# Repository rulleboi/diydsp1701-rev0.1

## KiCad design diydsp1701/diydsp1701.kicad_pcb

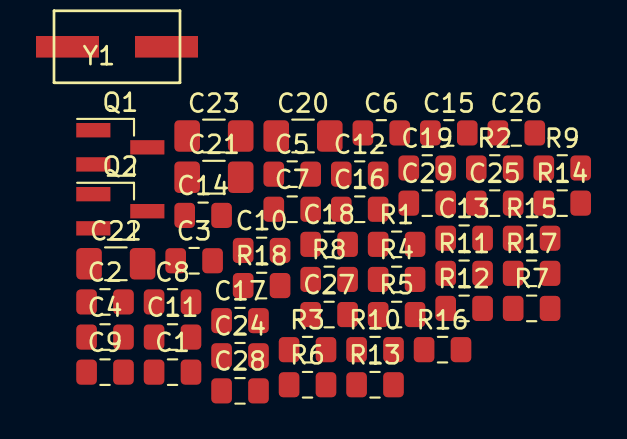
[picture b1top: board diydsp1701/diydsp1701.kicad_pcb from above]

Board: 2 copper layers, 50 parts (0 on the bottom side), 27 nets, no tracks yet.

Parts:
C1, C2: 100p; C_0805_2012Metric_Pad1.15x1.40mm_HandSolder
C3, C4, C7, C8, C12, C13: 10u; C_0805_2012Metric_Pad1.15x1.40mm_HandSolder
C5, C6, C9, C10, C11, C18, C19, C29: 100n; C_0805_2012Metric_Pad1.15x1.40mm_HandSolder
C14: 3n3; C_0805_2012Metric_Pad1.15x1.40mm_HandSolder
C15: 56n; C_0805_2012Metric_Pad1.15x1.40mm_HandSolder
C16, C17: 22p; C_0805_2012Metric_Pad1.15x1.40mm_HandSolder
C20, C21, C22, C23: 47u 4V; C_1206_3216Metric_Pad1.42x1.75mm_HandSolder
C24, C25, C26, C27: 5n6; C_0805_2012Metric_Pad1.15x1.40mm_HandSolder
C28: 330n; C_0805_2012Metric_Pad1.15x1.40mm_HandSolder
Q1: ZXTP25040DFH; SOT-23_Handsoldering
Q2: MMBT2222A-TP; SOT-23_Handsoldering
R1, R2: 47k; C_0805_2012Metric_Pad1.15x1.40mm_HandSolder
R3, R4, R5, R6: 18k0; C_0805_2012Metric_Pad1.15x1.40mm_HandSolder
R7: 1k; C_0805_2012Metric_Pad1.15x1.40mm_HandSolder
R8, R11, R12, R13, R14: 10k; C_0805_2012Metric_Pad1.15x1.40mm_HandSolder
R9: 100R; C_0805_2012Metric_Pad1.15x1.40mm_HandSolder
R10: 470R; C_0805_2012Metric_Pad1.15x1.40mm_HandSolder
R15, R16, R17, R18: 560R; C_0805_2012Metric_Pad1.15x1.40mm_HandSolder
Y1: 12.288MHz; ABLS7M2

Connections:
+1V8: C8.1, C9.1, C19.1, Q1.3, R14.2
+3V3: C14.1, C15.1, C18.1, C29.1, R3.2, R8.2, R11.2, R12.2, R13.2
/CM: C11.2, C13.2
/FILTA: C6.1, C7.1
/FILTD: C10.1, C12.1
/IN0: C1.1, C3.1, R1.2
/IN1: C2.1, C4.1, R2.2
/MCLKI: C16.1, Y1.2
/OUT0: C24.1, R15.1
/OUT1: C25.1, R16.1
/OUT2: C26.1, R17.1
/OUT3: C27.1, R18.1
/VDRIVE: Q1.1, R7.2
/_RESET: C5.1, R3.1
GND: C1.2, C2.2, C5.2, C6.2, C7.2, C8.2, C9.2, C10.2, C11.1, C12.2, C13.1, C16.2, C17.2, C18.2, C19.2, C24.2, C25.2, C26.2, C27.2, C28.2, C29.2, Q2.2, R1.1, R2.1, R5.2
unnamed: C3.2, R4.2
unnamed: C4.2, R6.2
unnamed: C14.2, R10.2
unnamed: C15.2, R10.1
unnamed: C17.1, R9.1, Y1.1
unnamed: C20.2, R15.2
unnamed: C21.2, R16.2
unnamed: C22.2, R17.2
unnamed: C23.2, R18.2
unnamed: Q1.2, R7.1
unnamed: Q2.1, R14.1
WB: Q2.3, R13.1

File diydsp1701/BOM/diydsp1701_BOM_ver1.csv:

Id;Designator;Package;Quantity;Designation;Supplier and ref;Price/per;Max total price DKK;Comment
1;U1;LQFP-48_7x7mm_Pitch0.5mm;1;ADAU1701JSTZ;http://www.digikey.dk/product-detail/en/analog-devices-inc/A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;72,9;72,9;locked
2;C1,C2;C_0805_HandSoldering;2;100p;http://www.digikey.dk/product-detail/en/kemet/C0805C101J5GAC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;0,68;1,36;
3;C3,C4,C7,C8,C12,C13;C_0805_HandSoldering;6;10u;http://www.digikey.dk/product-detail/en/murata-electronics-n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;0,95;5,7;
4;C5;C_0805_HandSoldering;1;10n;http://www.digikey.dk/product-detail/en/yageo/CC0805KRX7R9BB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;0,68;0,68;
5;C6,C9,C10,C11,C18,C19,C29;C_0805_HandSoldering;7;100n;http://www.digikey.dk/product-detail/en/avx-corporation/0805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;0,68;4,76;
6;C14;C_0805_HandSoldering;1;3n3;http://www.digikey.dk/product-detail/en/kemet/C0805C332K5RAC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;0,68;0,68;
7;C15;C_0805_HandSoldering;1;56n;http://www.digikey.dk/product-detail/en/samsung-electro-mech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;0,88;0,88;
8;C16,C17;C_0805_HandSoldering;2;22p;http://www.digikey.dk/product-detail/en/kemet/C0805C220J5GAC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;0,68;1,36;
9;C20,C21,C22,C23;C_0805_HandSoldering;4;47u 4V;http://www.digikey.dk/product-detail/en/kemet/T520A476M004AT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;6,95;27,8;1206
10;C24,C25,C26,C27;C_0805_HandSoldering;4;5n6;http://www.digikey.dk/product-detail/en/yageo/CC0805KRX7R9BB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;0,68;2,72;
11;P1,P5,P6;JST_PH_B3B-PH-K_03x2.00mm_Straight;3;CONN_01X03;http://www.digikey.dk/product-detail/en/jst-sales-america-in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;1,28;3,84;
12;R1,R2;R_0805_HandSoldering;2;47k;http://www.digikey.dk/product-detail/en/yageo/RC0805JR-0747K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;0,68;1,36;
13;R3,R4,R5,R6;R_0805_HandSoldering;4;18k0;http://www.digikey.dk/product-detail/en/yageo/RC0805FR-0718K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;0,68;2,72;1%
14;R7;R_0805_HandSoldering;1;1k;http://www.digikey.dk/product-detail/en/yageo/RC0805FR-071KL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;0,68;0,68;
15;R8,R11,R12,R13,R14;R_0805_HandSoldering;5;10k;http://www.digikey.dk/product-detail/en/yageo/RC0805JR-0710K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;0,68;3,4;
16;R9;R_0805_HandSoldering;1;100R;http://www.digikey.dk/product-detail/en/yageo/RC0805FR-07100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;0,68;0,68;
17;R10;R_0805_HandSoldering;1;470R;http://www.digikey.dk/product-detail/en/yageo/RC0805FR-07470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;0,68;0,68;
18;U2;SOIC-8_3.9x4.9mm_Pitch1.27mm;1;24AA256;http://www.digikey.dk/product-detail/en/microchip-technology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;5,13;5,13;locked
19;R15,R16,R17,R18;R_0805_HandSoldering;4;560R;http://www.digikey.dk/product-detail/en/yageo/RC0805FR-07560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;0,68;2,72;
20;Q2;SOT-23_Handsoldering;1;MMBT2222A-TP;http://www.digikey.dk/product-detail/en/micro-commercial-co/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;0,95;0,95;locked
21;Q1;SOT-23_Handsoldering;1;ZXTP25040DFH;http://www.digikey.dk/product-search/en?keywords=ZXTP25040DFH;3,92;3,92;locked
22;P2;Pin_Header_Straight_1x03;1;CONN_01X03;http://www.digikey.dk/product-detail/en/harwin-inc/M20-99903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;0,68;0,68;
23;P3;Pin_Header_Straight_1x02;1;CONN_01X02;http://www.digikey.dk/product-detail/en/harwin-inc/M20-99902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;0,68;0,68;
24;Y1;ABLS7M2;1;12.288MHz;http://www.digikey.dk/product-detail/en/abracon-llc/ABLS7M2-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;2,57;2,57;locked
25;C28;C_0805_HandSoldering;1;330n 25V;http://www.digikey.dk/product-detail/en/avx-corporation/0805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;0,68;0,68;
26;U3;SOT-223;1;UA78M33CDCYR;http://www.digikey.dk/product-detail/en/texas-instruments/UA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;3,92;3,92;locked
27;P7;JST_PH_B2B-PH-K_02x2.00mm_Straight;1;CONN_01X02;http://www.digikey.dk/product-detail/en/jst-sales-america-in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;1,15;1,15;
28;REF**,REF**,REF**,REF**;MountingHole_3.2mm_M3_Pad_Via;4;MountingHole_3.2mm_M3_Pad_Via;-;0;0;
29;P4;Pin_Header_Straight_1x12;1;CONN_01X12;http://www.digikey.dk/product-detail/en/sullins-connector-so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;2,23;2,23;
;;;;;;;156,83;

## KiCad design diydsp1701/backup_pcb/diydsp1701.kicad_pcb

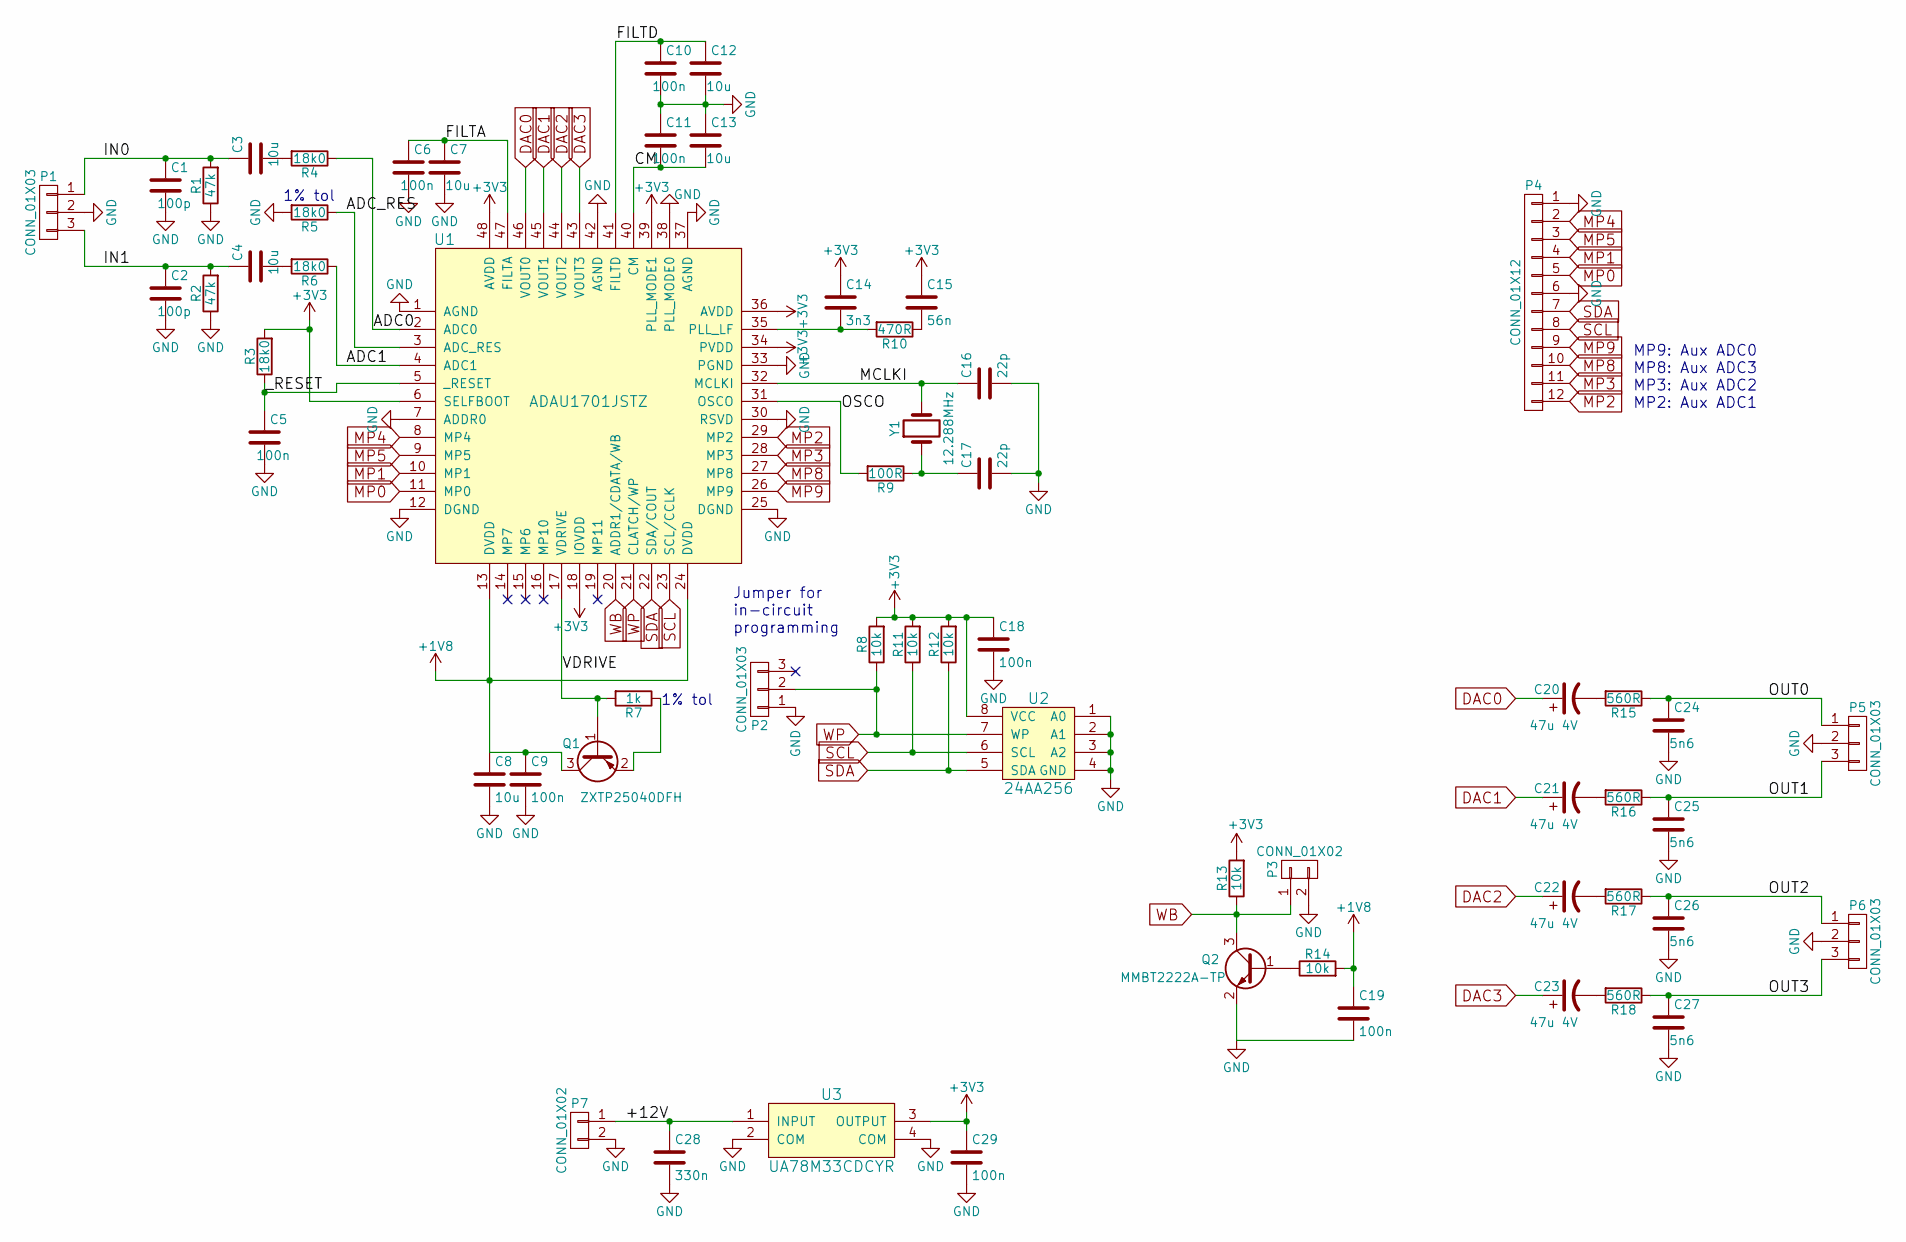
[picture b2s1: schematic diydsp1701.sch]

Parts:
C1, C2: 100p; C_0805_2012Metric_Pad1.15x1.40mm_HandSolder
C3, C4, C7, C8, C12, C13: 10u; C_0805_2012Metric_Pad1.15x1.40mm_HandSolder
C5, C6, C9, C10, C11, C18, C19, C29: 100n; C_0805_2012Metric_Pad1.15x1.40mm_HandSolder
C14: 3n3; C_0805_2012Metric_Pad1.15x1.40mm_HandSolder
C15: 56n; C_0805_2012Metric_Pad1.15x1.40mm_HandSolder
C16, C17: 22p; C_0805_2012Metric_Pad1.15x1.40mm_HandSolder
C20, C21, C22, C23: 47u 4V; C_1206_3216Metric_Pad1.42x1.75mm_HandSolder
C24, C25, C26, C27: 5n6; C_0805_2012Metric_Pad1.15x1.40mm_HandSolder
C28: 330n; C_0805_2012Metric_Pad1.15x1.40mm_HandSolder
P1, P5, P6: CONN_01X03; JST_PH_B3B-PH-K_03x2.00mm_Straight
P2: CONN_01X03; Pin_Header_Straight_1x03
P3: CONN_01X02; Pin_Header_Straight_1x02
P4: CONN_01X12; Pin_Header_Straight_1x12
P7: CONN_01X02; JST_PH_B2B-PH-K_02x2.00mm_Straight
Q1: ZXTP25040DFH; SOT-23_Handsoldering
Q2: MMBT2222A-TP; SOT-23_Handsoldering
R1, R2: 47k; C_0805_2012Metric_Pad1.15x1.40mm_HandSolder
R3, R4, R5, R6: 18k0; C_0805_2012Metric_Pad1.15x1.40mm_HandSolder
R7: 1k; C_0805_2012Metric_Pad1.15x1.40mm_HandSolder
R8, R11, R12, R13, R14: 10k; C_0805_2012Metric_Pad1.15x1.40mm_HandSolder
R9: 100R; C_0805_2012Metric_Pad1.15x1.40mm_HandSolder
R10: 470R; C_0805_2012Metric_Pad1.15x1.40mm_HandSolder
R15, R16, R17, R18: 560R; C_0805_2012Metric_Pad1.15x1.40mm_HandSolder
U1: ADAU1701JSTZ; LQFP-48_7x7mm_Pitch0.5mm
U2: 24AA256; SOIC-8_3.9x4.9mm_Pitch1.27mm
U3: UA78M33CDCYR; SOT-223
Y1: 12.288MHz; ABLS7M2

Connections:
+1V8: C8.1, C9.1, C19.1, Q1.3 (C), R14.2, U1.13 (DVDD), U1.24 (DVDD)
+3V3: C14.1, C15.1, C18.1, C29.1, R3.2, R8.2, R11.2, R12.2, R13.2, U1.6 (SELFBOOT), U1.18 (IOVDD), U1.34 (PVDD), U1.36 (AVDD), U1.39 (PLL_MODE1), U1.48 (AVDD), U2.8 (VCC), U3.3 (OUTPUT)
/+12V: C28.1, P7.1, U3.1 (INPUT)
/ADC0: R4.1, U1.2 (ADC0)
/ADC1: R6.1, U1.4 (ADC1)
/ADC_RES: R5.1, U1.3 (ADC_RES)
/CM: C11.2, C13.2, U1.40 (CM)
/FILTA: C6.1, C7.1, U1.47 (FILTA)
/FILTD: C10.1, C12.1, U1.41 (FILTD)
/IN0: C1.1, C3.1, P1.1, R1.2
/IN1: C2.1, C4.1, P1.3, R2.2
/MCLKI: C16.1, U1.32 (MCLKI), Y1.2
/OSCO: R9.2, U1.31 (OSCO)
/OUT0: C24.1, P5.1, R15.1
/OUT1: C25.1, P5.3, R16.1
/OUT2: C26.1, P6.1, R17.1
/OUT3: C27.1, P6.3, R18.1
/VDRIVE: Q1.1 (B), R7.2, U1.17 (VDRIVE)
/_RESET: C5.1, R3.1, U1.5 (_RESET)
DAC0: C20.1, U1.46 (VOUT0)
DAC1: C21.1, U1.45 (VOUT1)
DAC2: C22.1, U1.44 (VOUT2)
DAC3: C23.1, U1.43 (VOUT3)
GND: C1.2, C2.2, C5.2, C6.2, C7.2, C8.2, C9.2, C10.2, C11.1, C12.2, C13.1, C16.2, C17.2, C18.2, C19.2, C24.2, C25.2, C26.2, C27.2, C28.2, C29.2, P1.2, P2.1, P3.2, P4.1, P4.6, P5.2, P6.2, P7.2, Q2.2 (E), R1.1, R2.1, R5.2, U1.1 (AGND), U1.7 (ADDR0), U1.12 (DGND), U1.25 (DGND), U1.30 (RSVD), U1.33 (PGND), U1.37 (AGND), U1.38 (PLL_MODE0), U1.42 (AGND), U2.1 (A0), U2.2 (A1), U2.3 (A2), U2.4 (GND), U3.2 (COM), U3.4 (COM)
MP0: P4.5, U1.11 (MP0)
MP1: P4.4, U1.10 (MP1)
MP2: P4.12, U1.29 (MP2)
MP3: P4.11, U1.28 (MP3)
MP4: P4.2, U1.8 (MP4)
MP5: P4.3, U1.9 (MP5)
MP8: P4.10, U1.27 (MP8)
MP9: P4.9, U1.26 (MP9)
unnamed: C3.2, R4.2
unnamed: C4.2, R6.2
unnamed: C14.2, R10.2, U1.35 (PLL_LF)
unnamed: C15.2, R10.1
unnamed: C17.1, R9.1, Y1.1
unnamed: C20.2, R15.2
unnamed: C21.2, R16.2
unnamed: C22.2, R17.2
unnamed: C23.2, R18.2
unnamed: Q1.2 (E), R7.1
unnamed: Q2.1 (B), R14.1
SCL: P4.8, R11.1, U1.23 (SCL/CCLK), U2.6 (SCL)
SDA: P4.7, R12.1, U1.22 (SDA/COUT), U2.5 (SDA)
WB: P3.1, Q2.3 (C), R13.1, U1.20 (ADDR1/CDATA/WB)
WP: P2.2, R8.1, U1.21 (CLATCH/WP), U2.7 (WP)

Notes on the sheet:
1% tol
Jumper for in-circuit programming
MP9: Aux ADC0 MP8: Aux ADC3 MP3: Aux ADC2 MP2: Aux ADC1

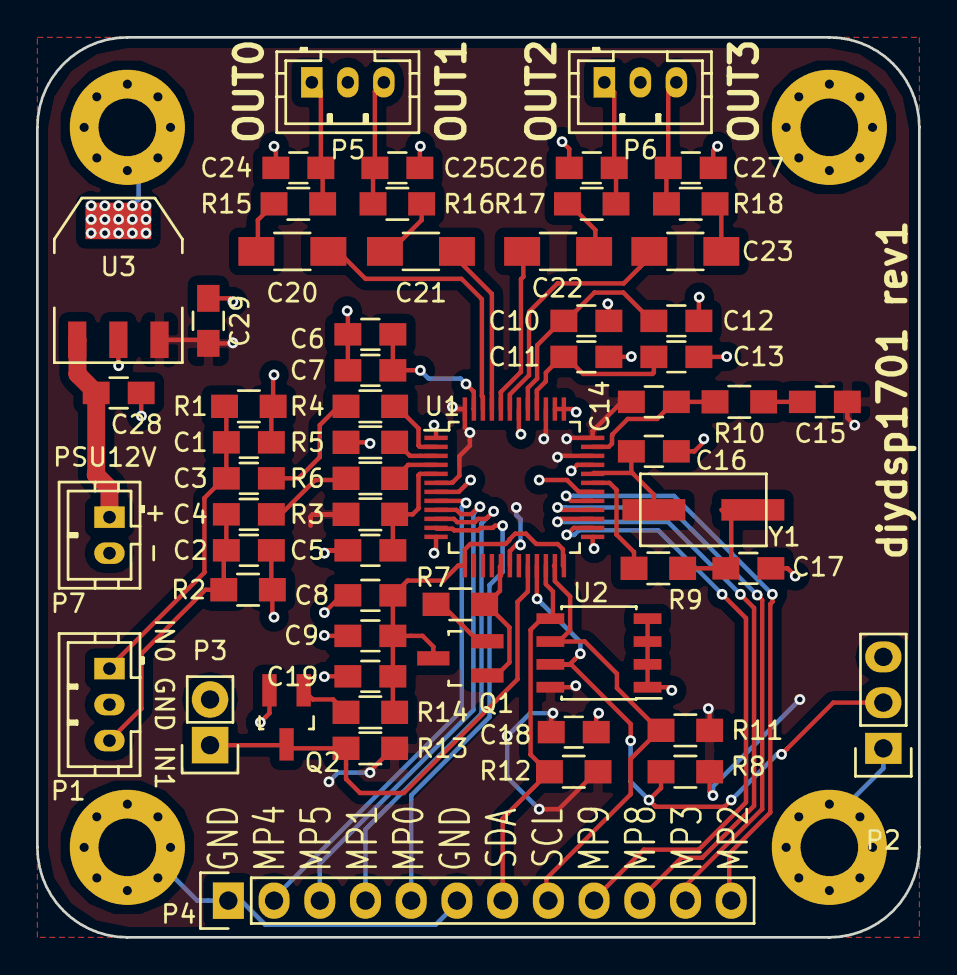
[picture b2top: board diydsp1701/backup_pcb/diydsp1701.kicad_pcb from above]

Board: 2 copper layers, 49.0 x 50.0 mm, 60 parts (0 on the bottom side), 47 nets.

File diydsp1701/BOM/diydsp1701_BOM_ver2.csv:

Id;Designator;Package;Quantity;Designation;Supplier and ref;Price/per;Max total price DKK;Comment;Amount to buy 14 Nov 2016
1;U1;LQFP-48_7x7mm_Pitch0.5mm;1;ADAU1701JSTZ;http://www.digikey.dk/product-detail/en/analog-devices-inc/A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;72,9;72,9;locked;2
2;C1,C2;C_0805_HandSoldering;2;100p;http://www.digikey.dk/product-detail/en/kemet/C0805C101J5GAC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;0,68;1,36;;
3;C3,C4,C7,C8,C12,C13;C_0805_HandSoldering;6;10u;http://www.digikey.dk/product-detail/en/murata-electronics-n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;0,95;5,7;;
4;C5;C_0805_HandSoldering;1;10n;http://www.digikey.dk/product-detail/en/yageo/CC0805KRX7R9BB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;0,68;0,68;;
5;C6,C9,C10,C11,C18,C19,C29;C_0805_HandSoldering;7;100n;http://www.digikey.dk/product-detail/en/avx-corporation/0805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;0,68;4,76;;
6;C14;C_0805_HandSoldering;1;3n3;http://www.digikey.dk/product-detail/en/kemet/C0805C332K5RAC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;0,68;0,68;;
7;C15;C_0805_HandSoldering;1;56n;http://www.digikey.dk/product-detail/en/samsung-electro-mech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;0,88;0,88;;
8;C16,C17;C_0805_HandSoldering;2;22p;http://www.digikey.dk/product-detail/en/kemet/C0805C220J5GAC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;0,68;1,36;;
9;C24,C25,C26,C27;C_0805_HandSoldering;4;5n6;http://www.digikey.dk/product-detail/en/kemet/T520A476M004AT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;6,95;27,8;1206;
10;P1,P5,P6;JST_PH_B3B-PH-K_03x2.00mm_Straight;3;CONN_01X03;http://www.digikey.dk/product-detail/en/yageo/CC0805KRX7R9BB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;0,68;2,72;;
11;R1,R2;R_0805_HandSoldering;2;47k;http://www.digikey.dk/product-detail/en/jst-sales-america-in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;1,28;3,84;;
12;R3,R4,R5,R6;R_0805_HandSoldering;4;18k0;http://www.digikey.dk/product-detail/en/yageo/RC0805JR-0747K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;0,68;1,36;;
13;R7;R_0805_HandSoldering;1;1k;http://www.digikey.dk/product-detail/en/yageo/RC0805FR-0718K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;0,68;2,72;1%;
14;R8,R11,R12,R13,R14;R_0805_HandSoldering;5;10k;http://www.digikey.dk/product-detail/en/yageo/RC0805FR-071KL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;0,68;0,68;;
15;R9;R_0805_HandSoldering;1;100R;http://www.digikey.dk/product-detail/en/yageo/RC0805JR-0710K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;0,68;3,4;;
16;R10;R_0805_HandSoldering;1;470R;http://www.digikey.dk/product-detail/en/yageo/RC0805FR-07100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;0,68;0,68;;
17;U2;SOIC-8_3.9x4.9mm_Pitch1.27mm;1;24AA256;http://www.digikey.dk/product-detail/en/yageo/RC0805FR-07470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;0,68;0,68;;
18;R15,R16,R17,R18;R_0805_HandSoldering;4;560R;http://www.digikey.dk/product-detail/en/microchip-technology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;5,13;5,13;locked;
19;Q2;SOT-23_Handsoldering;1;MMBT2222A-TP;http://www.digikey.dk/product-detail/en/yageo/RC0805FR-07560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;0,68;2,72;;
20;Q1;SOT-23_Handsoldering;1;ZXTP25040DFH;http://www.digikey.dk/product-detail/en/micro-commercial-co/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;0,95;0,95;locked;
21;P2;Pin_Header_Straight_1x03;1;CONN_01X03;http://www.digikey.dk/product-search/en?keywords=ZXTP25040DFH;3,92;3,92;locked;
22;P3;Pin_Header_Straight_1x02;1;CONN_01X02;http://www.digikey.dk/product-detail/en/harwin-inc/M20-99903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;0,68;0,68;;
23;Y1;ABLS7M2;1;12.288MHz;http://www.digikey.dk/product-detail/en/harwin-inc/M20-99902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;0,68;0,68;;
24;C28;C_0805_HandSoldering;1;330n;http://www.digikey.dk/product-detail/en/abracon-llc/ABLS7M2-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;2,57;2,57;locked;
25;U3;SOT-223;1;UA78M33CDCYR;http://www.digikey.dk/product-detail/en/avx-corporation/0805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;0,68;0,68;;
26;P7;JST_PH_B2B-PH-K_02x2.00mm_Straight;1;CONN_01X02;http://www.digikey.dk/product-detail/en/texas-instruments/UA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;3,92;3,92;locked;
27;REF**,REF**,REF**,REF**;MountingHole_3.2mm_M3_Pad_Via;4;MountingHole_3.2mm_M3_Pad_Via;http://www.digikey.dk/product-detail/en/jst-sales-america-in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;1,15;1,15;;
28;P4;Pin_Header_Straight_1x12;1;CONN_01X12;-;0;0;;
29;C20,C21,C22,C23;C_1206_HandSoldering;4;47u 4V;http://www.digikey.dk/product-detail/en/sullins-connector-so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;2,23;2,23;;
